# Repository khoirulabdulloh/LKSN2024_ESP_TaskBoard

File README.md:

# LKSN2024_ESP_TaskBoard
Embedded System Programming Task Board for Lomba Kompetensi Siswa Nasional Tahun 2024

 -Template_Program berisi template untuk pemrogramaan saat lomba, template akan terus update hingga H-3 perlombaan
 
 -file *.sch* merupakan schematic file EAGLE atau Fusion360

 -file *.brd* merupakan layout file EAGLE atau Fusion360

 -Schematic .pdf merupakan schematic file yang sudah di export dalam PDF

 -file .png merupakan foto dari TaskProject

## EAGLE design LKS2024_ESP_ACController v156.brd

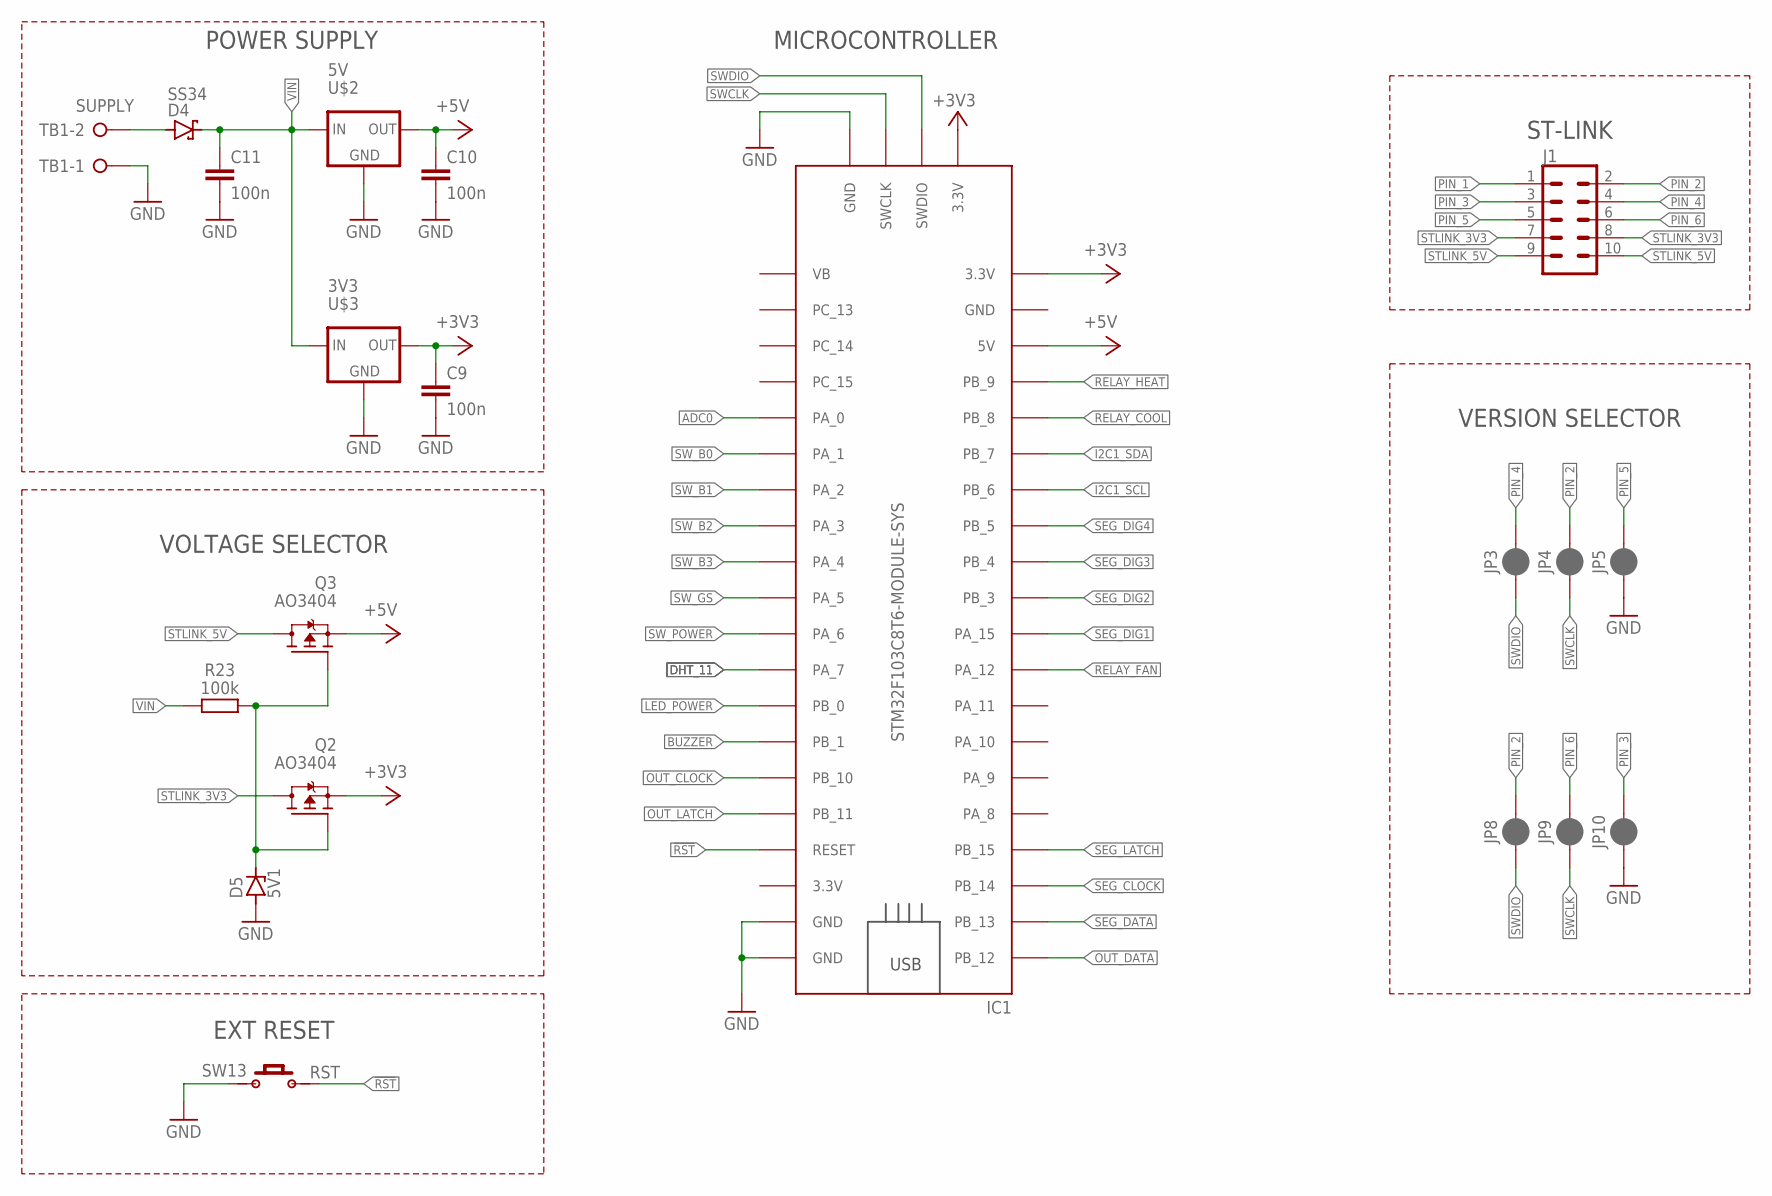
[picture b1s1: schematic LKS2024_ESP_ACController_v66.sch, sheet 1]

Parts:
C9, C10, C11: 100n; C0805
D4: SS34; SMA
D5: 5V1; SOD80C
IC1: STM32F103C8T6-MODULE-SYS
J1: CONN_05X2ML10L; ML10L
JP3, JP4, JP5, JP8, JP9, JP10: JUMPER-SMT_2_NC_PASTE_SILK; SMT-JUMPER_2_NC_PASTE_SILK
Q2, Q3: AO3404; SOT23
R23: 100k; R0805
SW13: RST; PUSH_BUTTON_2P
TB1: SUPPLY; MSTBA2
U$2: 5V; SOT223
U$3: 3V3; SOT223

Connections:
!RST: IC1.RESET, SW13.2
+3V3: C9.1, IC1.3.3V_1 (3.3V), IC1.3V3_1 (3.3V), IC1.3V3_3 (3.3V), Q2.2 (S), U$3.2 (OUT); also elsewhere on the board
+5V: C10.1, IC1.5V, Q3.2 (S), U$2.2 (OUT); also elsewhere on the board
ADC0: IC1.PA_0; also elsewhere on the board
BUZZER: IC1.PB_1; also elsewhere on the board
DHT_11: IC1.PA_7; also elsewhere on the board
GND: C9.2, C10.2, C11.2, D5.A, IC1.GND_2 (GND), IC1.GND_3 (GND), IC1.GND_4 (GND), IC1.GND_5 (GND), JP5.1, JP10.1, SW13.1, TB1.1, U$2.1 (GND), U$3.1 (GND); also elsewhere on the board
I2C1_SCL: IC1.PB_6; also elsewhere on the board
I2C1_SDA: IC1.PB_7; also elsewhere on the board
LED_POWER: IC1.PB_0; also elsewhere on the board
unnamed: D4.A, TB1.2
unnamed: D5.C, Q2.1 (G), Q3.1 (G), R23.2
OUT_CLOCK: IC1.PB_10; also elsewhere on the board
OUT_DATA: IC1.PB_12; also elsewhere on the board
OUT_LATCH: IC1.PB_11; also elsewhere on the board
PIN_1: J1.1
PIN_2: J1.2, JP4.2, JP8.2
PIN_3: J1.3, JP10.2
PIN_4: J1.4, JP3.2
PIN_5: J1.5, JP5.2
PIN_6: J1.6, JP9.2
RELAY_COOL: IC1.PB_8; also elsewhere on the board
RELAY_FAN: IC1.PA_12; also elsewhere on the board
RELAY_HEAT: IC1.PB_9; also elsewhere on the board
SEG_CLOCK: IC1.PB_14; also elsewhere on the board
SEG_DATA: IC1.PB_13; also elsewhere on the board
SEG_DIG1: IC1.PA_15; also elsewhere on the board
SEG_DIG2: IC1.PB_3; also elsewhere on the board
SEG_DIG3: IC1.PB_4; also elsewhere on the board
SEG_DIG4: IC1.PB_5; also elsewhere on the board
SEG_LATCH: IC1.PB_15; also elsewhere on the board
STLINK_3V3: J1.7, J1.8, Q2.3 (D)
STLINK_5V: J1.9, J1.10, Q3.3 (D)
SWCLK: IC1.SWCLK, IC1.SWCLK1 (SWCLK), JP4.1, JP9.1
SWDIO: IC1.SWDIO, IC1.SWDIO1 (SWDIO), JP3.1, JP8.1
SW_B0: IC1.PA_1; also elsewhere on the board
SW_B1: IC1.PA_2; also elsewhere on the board
SW_B2: IC1.PA_3; also elsewhere on the board
SW_B3: IC1.PA_4; also elsewhere on the board
SW_GS: IC1.PA_5; also elsewhere on the board
SW_POWER: IC1.PA_6; also elsewhere on the board
VIN: C11.1, D4.C, R23.1, U$2.3 (IN), U$3.3 (IN)

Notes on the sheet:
POWER SUPPLY
VOLTAGE SELECTOR
EXT RESET
ST-LINK
VERSION SELECTOR
MICROCONTROLLER

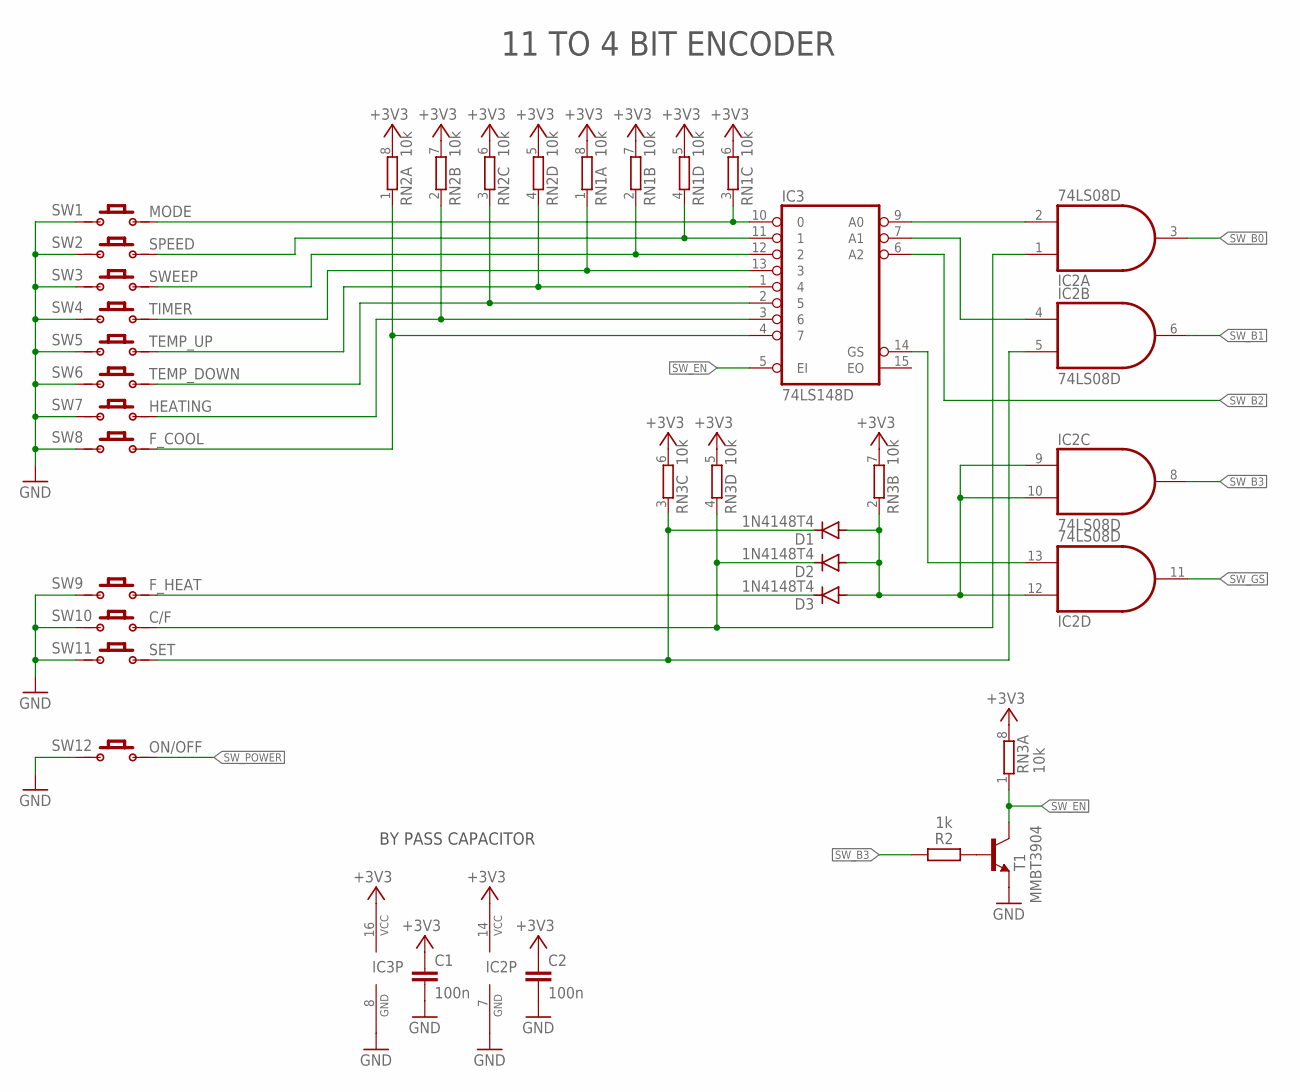
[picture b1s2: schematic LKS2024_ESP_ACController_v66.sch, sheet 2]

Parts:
C1, C2: 100n; C0805
D1, D2, D3: 1N4148T4; SOD123
IC2: 74LS08D; SO14
IC3: 74LS148D; SO16
R2: 1k; R0805
RN1, RN2, RN3: 10k; 0603-ARC
SW1: MODE; PUSH_BUTTON_2P
SW2: SPEED; PUSH_BUTTON_2P
SW3: SWEEP; PUSH_BUTTON_2P
SW4: TIMER; PUSH_BUTTON_2P
SW5: TEMP_UP; PUSH_BUTTON_2P
SW6: TEMP_DOWN; PUSH_BUTTON_2P
SW7: HEATING; PUSH_BUTTON_2P
SW8: F_COOL; PUSH_BUTTON_2P
SW9: F_HEAT; PUSH_BUTTON_2P
SW10: C/F; PUSH_BUTTON_2P
SW11: SET; PUSH_BUTTON_2P
SW12: ON/OFF; PUSH_BUTTON_2P
T1: MMBT3904; SOT23-BEC

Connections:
+3V3: C1.1, C2.1, IC2.14 (VCC), IC3.16 (VCC), RN1.5 (2), RN1.6 (2), RN1.7 (2), RN1.8 (2), RN2.5 (2), RN2.6 (2), RN2.7 (2), RN2.8 (2), RN3.5 (2), RN3.6 (2), RN3.7 (2), RN3.8 (2); also elsewhere on the board
GND: C1.2, C2.2, IC2.7 (GND), IC3.8 (GND), SW1.1, SW2.1, SW3.1, SW4.1, SW5.1, SW6.1, SW7.1, SW8.1, SW9.1, SW10.1, SW11.1, SW12.1, T1.E; also elsewhere on the board
unnamed: IC2.2 (I1), IC3.9 (A0)
unnamed: IC2.4 (I0), IC3.7 (A1)
unnamed: IC2.13 (I1), IC3.14 (GS)
unnamed: D1.A, D2.A, D3.A, IC2.9 (I0), IC2.10 (I1), IC2.12 (I0), RN3.2 (1)
unnamed: IC3.10 (0), RN1.3 (1), SW1.2
unnamed: IC3.11 (1), RN1.4 (1), SW2.2
unnamed: IC3.12 (2), RN1.2 (1), SW3.2
unnamed: IC3.13 (3), RN1.1, SW4.2
unnamed: IC3.1 (4), RN2.4 (1), SW5.2
unnamed: IC3.2 (5), RN2.3 (1), SW6.2
unnamed: IC3.3 (6), RN2.2 (1), SW7.2
unnamed: IC3.4 (7), RN2.1, SW8.2
unnamed: D3.C, SW9.2
unnamed: D2.C, IC2.1 (I0), RN3.4 (1), SW10.2
unnamed: D1.C, IC2.5 (I1), RN3.3 (1), SW11.2
unnamed: R2.1, T1.B
SW_B0: IC2.3 (O); also elsewhere on the board
SW_B1: IC2.6 (O); also elsewhere on the board
SW_B2: IC3.6 (A2); also elsewhere on the board
SW_B3: IC2.8 (O), R2.2; also elsewhere on the board
SW_EN: IC3.5 (EI), RN3.1, T1.C
SW_GS: IC2.11 (O); also elsewhere on the board
SW_POWER: SW12.2; also elsewhere on the board

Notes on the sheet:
11 TO 4 BIT ENCODER
BY PASS CAPACITOR

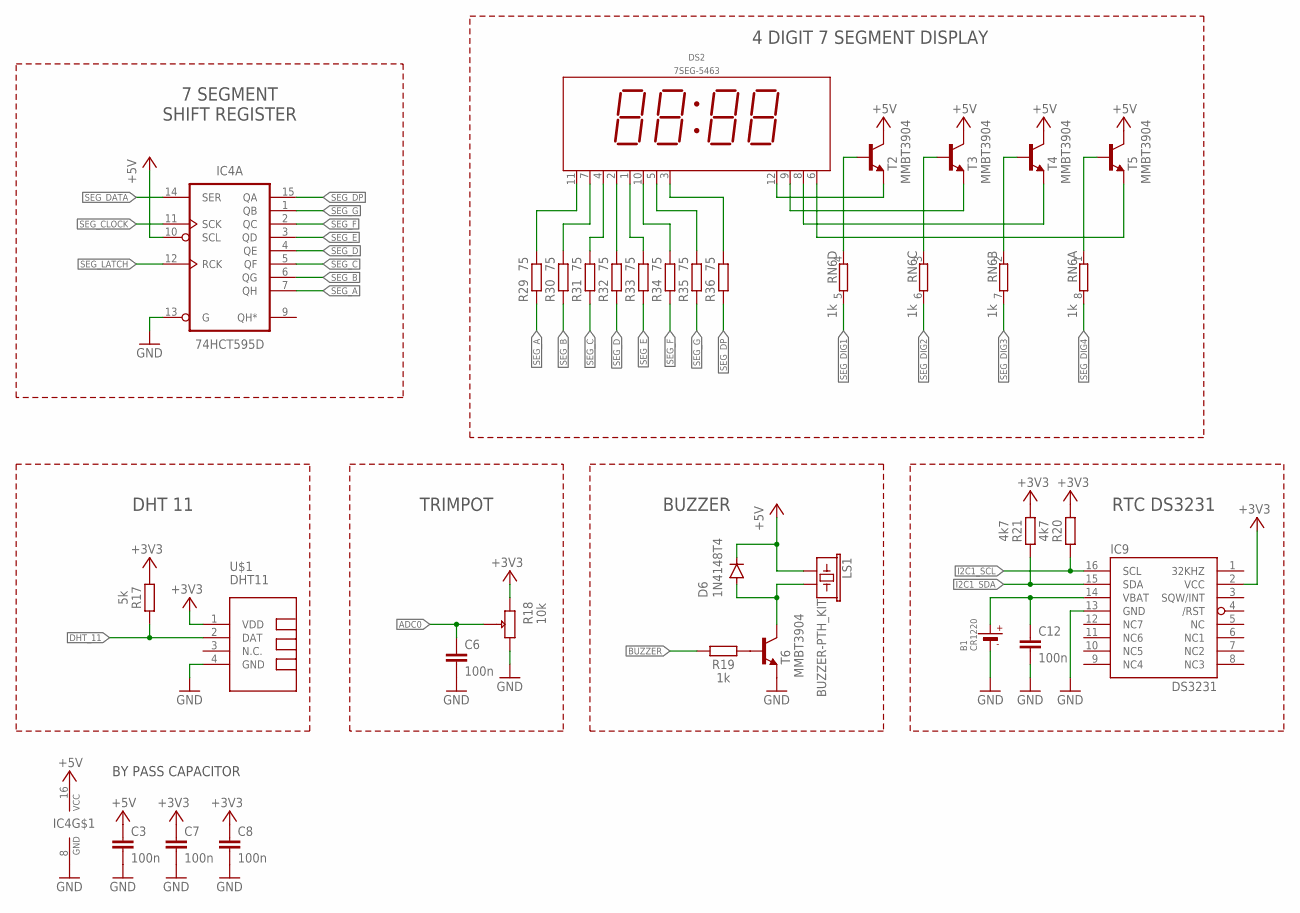
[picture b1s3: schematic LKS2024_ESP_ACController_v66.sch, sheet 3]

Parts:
B1: CR1220
C3, C6, C7, C8, C12: 100n; C0805
D6: 1N4148T4; SOD123
DS2: 7SEG-5463; 5643
IC4: 74HCT595D; SO16
IC9: DS3231"; SO16W
LS1: BUZZER-PTH_KIT; BUZZER-12MM-KIT
R17: 5k; R0805
R18: 10k; TRIM_3386P-1-101T
R19: 1k; R0805
R20, R21: 4k7; R0805
R29, R30, R31, R32, R33, R34, R35, R36: 75; R0603
RN6: 1k; 0603-ARC
T2, T3, T4, T5, T6: MMBT3904; SOT23-BEC
U$1: DHT11

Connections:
+3V3: C7.1, C8.1, IC9.2 (VCC), R17.1, R18.3 (CW), R20.2, R21.2, U$1.1 (VDD); also elsewhere on the board
+5V: C3.1, D6.C, IC4.10 (SCL), IC4.16 (VCC), LS1.+\ (1), T2.C, T3.C, T4.C, T5.C; also elsewhere on the board
ADC0: C6.1, R18.2 (WIPER); also elsewhere on the board
BUZZER: R19.1; also elsewhere on the board
DHT_11: R17.2, U$1.2 (DAT); also elsewhere on the board
GND: B1.-, C3.2, C6.2, C7.2, C8.2, C12.2, IC4.8 (GND), IC4.13 (G), IC9.13 (GND), R18.1 (CCW), T6.E, U$1.4 (GND); also elsewhere on the board
I2C1_SCL: IC9.16 (SCL), R20.1; also elsewhere on the board
I2C1_SDA: IC9.15 (SDA), R21.1; also elsewhere on the board
unnamed: DS2.12 (DIG1), T2.E
unnamed: DS2.11 (A), R29.2
unnamed: DS2.7 (B), R30.2
unnamed: DS2.4 (C), R31.2
unnamed: DS2.2 (D), R32.2
unnamed: DS2.1 (E), R33.2
unnamed: DS2.10 (F), R34.2
unnamed: DS2.5 (G), R35.2
unnamed: DS2.3 (H), R36.2
unnamed: RN6.4 (1), T2.B
unnamed: DS2.9 (DIG2), T3.E
unnamed: DS2.8 (DIG3), T4.E
unnamed: DS2.6 (DIG4), T5.E
unnamed: RN6.3 (1), T3.B
unnamed: RN6.2 (1), T4.B
unnamed: RN6.1, T5.B
unnamed: D6.A, LS1.- (2), T6.C
unnamed: R19.2, T6.B
unnamed: B1.+, C12.1, IC9.14 (VBAT)
SEG_A: IC4.7 (QH), R29.1
SEG_B: IC4.6 (QG), R30.1
SEG_C: IC4.5 (QF), R31.1
SEG_CLOCK: IC4.11 (SCK); also elsewhere on the board
SEG_D: IC4.4 (QE), R32.1
SEG_DATA: IC4.14 (SER); also elsewhere on the board
SEG_DIG1: RN6.5 (2); also elsewhere on the board
SEG_DIG2: RN6.6 (2); also elsewhere on the board
SEG_DIG3: RN6.7 (2); also elsewhere on the board
SEG_DIG4: RN6.8 (2); also elsewhere on the board
SEG_DP: IC4.15 (QA), R36.1
SEG_E: IC4.3 (QD), R33.1
SEG_F: IC4.2 (QC), R34.1
SEG_G: IC4.1 (QB), R35.1
SEG_LATCH: IC4.12 (RCK); also elsewhere on the board

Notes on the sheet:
4 DIGIT 7 SEGMENT DISPLAY
7 SEGMENT SHIFT REGISTER
RTC DS3231
BUZZER
TRIMPOT
DHT 11
BY PASS CAPACITOR

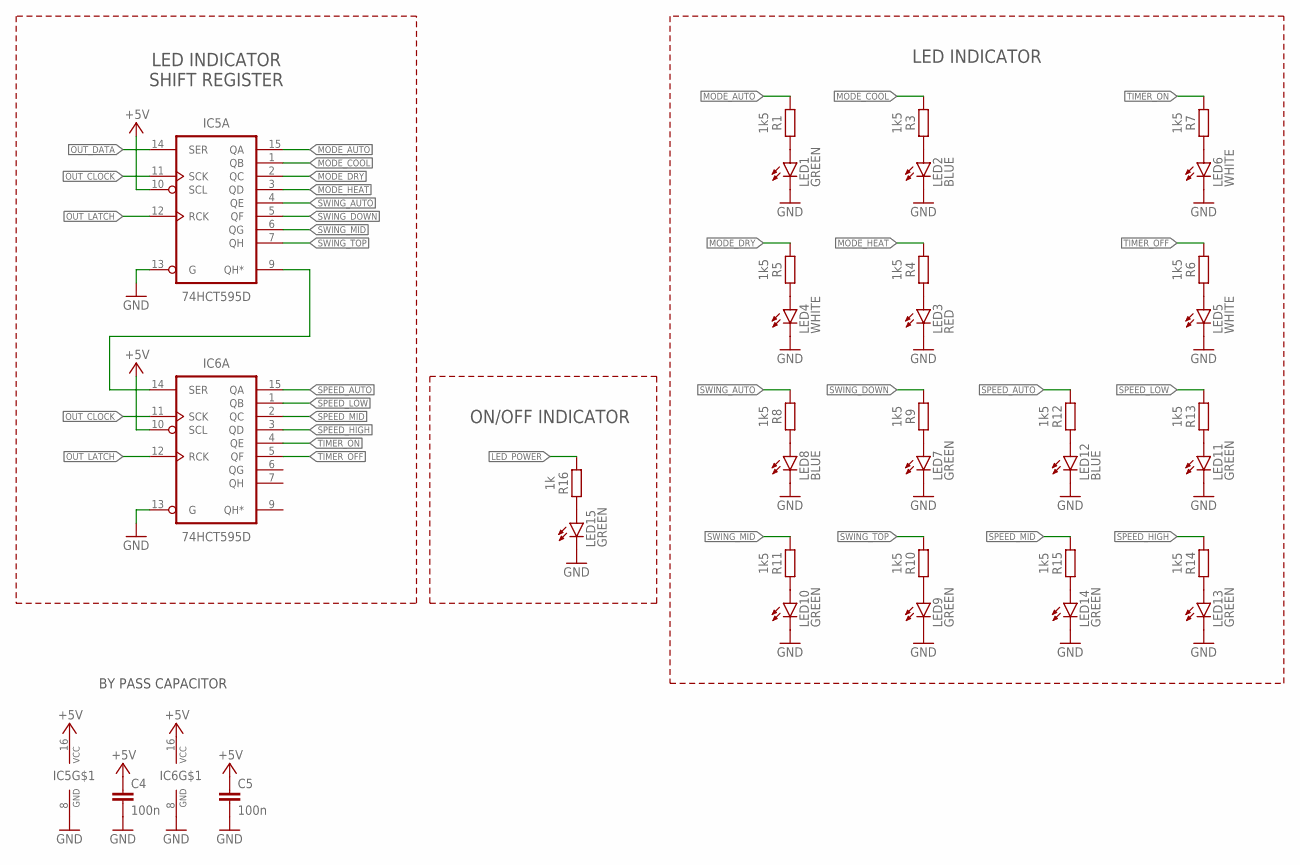
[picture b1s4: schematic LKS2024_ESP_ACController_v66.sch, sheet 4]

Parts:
C4, C5: 100n; C0805
IC5, IC6: 74HCT595D; SO16
LED1, LED7, LED9, LED10, LED11, LED13, LED14, LED15: GREEN; CHIPLED_1206
LED2, LED8, LED12: BLUE; CHIPLED_1206
LED3: RED; CHIPLED_1206
LED4, LED5, LED6: WHITE; CHIPLED_1206
R1, R3, R4, R5, R6, R7, R8, R9, R10, R11, R12, R13, R14, R15: 1k5; R0805
R16: 1k; R0805

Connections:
+5V: C4.1, C5.1, IC5.10 (SCL), IC5.16 (VCC), IC6.10 (SCL), IC6.16 (VCC); also elsewhere on the board
GND: C4.2, C5.2, IC5.8 (GND), IC5.13 (G), IC6.8 (GND), IC6.13 (G), LED1.C, LED2.C, LED3.C, LED4.C, LED5.C, LED6.C, LED7.C, LED8.C, LED9.C, LED10.C, LED11.C, LED12.C, LED13.C, LED14.C, LED15.C; also elsewhere on the board
LED_POWER: R16.1; also elsewhere on the board
MODE_AUTO: IC5.15 (QA), R1.1
MODE_COOL: IC5.1 (QB), R3.1
MODE_DRY: IC5.2 (QC), R5.1
MODE_HEAT: IC5.3 (QD), R4.1
unnamed: IC5.9 (QH*), IC6.14 (SER)
unnamed: LED1.A, R1.2
unnamed: LED2.A, R3.2
unnamed: LED3.A, R4.2
unnamed: LED4.A, R5.2
unnamed: LED5.A, R6.2
unnamed: LED6.A, R7.2
unnamed: LED8.A, R8.2
unnamed: LED7.A, R9.2
unnamed: LED9.A, R10.2
unnamed: LED10.A, R11.2
unnamed: LED12.A, R12.2
unnamed: LED11.A, R13.2
unnamed: LED13.A, R14.2
unnamed: LED14.A, R15.2
unnamed: LED15.A, R16.2
OUT_CLOCK: IC5.11 (SCK), IC6.11 (SCK); also elsewhere on the board
OUT_DATA: IC5.14 (SER); also elsewhere on the board
OUT_LATCH: IC5.12 (RCK), IC6.12 (RCK); also elsewhere on the board
SPEED_AUTO: IC6.15 (QA), R12.1
SPEED_HIGH: IC6.3 (QD), R14.1
SPEED_LOW: IC6.1 (QB), R13.1
SPEED_MID: IC6.2 (QC), R15.1
SWING_AUTO: IC5.4 (QE), R8.1
SWING_DOWN: IC5.5 (QF), R9.1
SWING_MID: IC5.6 (QG), R11.1
SWING_TOP: IC5.7 (QH), R10.1
TIMER_OFF: IC6.5 (QF), R6.1
TIMER_ON: IC6.4 (QE), R7.1

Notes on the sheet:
LED INDICATOR
ON/OFF INDICATOR
LED INDICATOR SHIFT REGISTER
BY PASS CAPACITOR

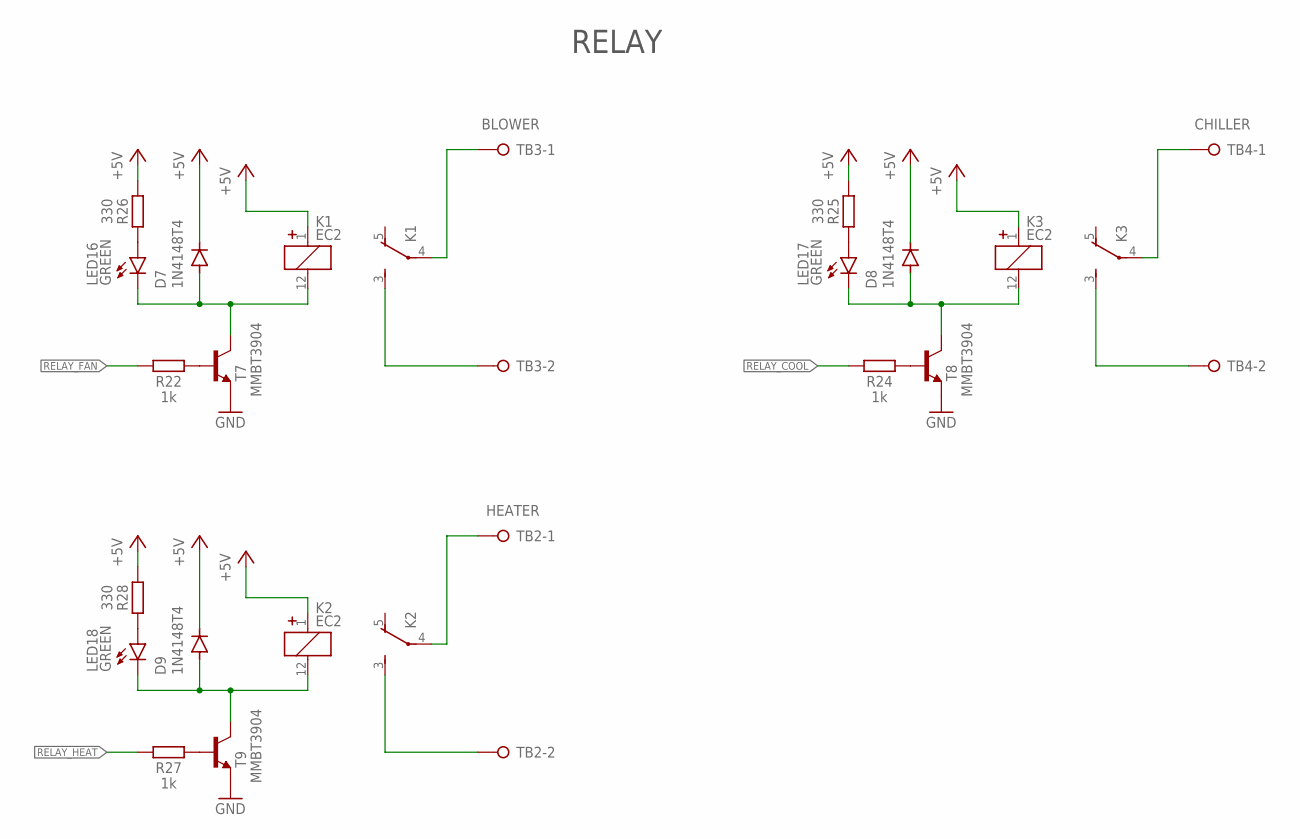
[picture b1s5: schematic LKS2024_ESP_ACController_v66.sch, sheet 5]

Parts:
D7, D8, D9: 1N4148T4; SOD123
K1, K2, K3: EC2
LED16, LED17, LED18: GREEN; CHIPLED_1206
R22, R24, R27: 1k; R0805
R25, R26, R28: 330; R0805
T7, T8, T9: MMBT3904; SOT23-BEC
TB2: HEATER; MSTBA2
TB3: BLOWER; MSTBA2
TB4: CHILLER; MSTBA2

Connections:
+5V: D7.C, D8.C, D9.C, K1.1 (1+), K2.1 (1+), K3.1 (1+), R25.1, R26.1, R28.1; also elsewhere on the board
GND: T7.E, T8.E, T9.E; also elsewhere on the board
unnamed: D7.A, K1.12 (2-), LED16.C, T7.C
unnamed: R22.2, T7.B
unnamed: D8.A, K3.12 (2-), LED17.C, T8.C
unnamed: R24.2, T8.B
unnamed: LED17.A, R25.2
unnamed: K3.3 (S), TB4.2
unnamed: LED16.A, R26.2
unnamed: K1.3 (S), TB3.2
unnamed: K1.4, TB3.1
unnamed: K3.4, TB4.1
unnamed: D9.A, K2.12 (2-), LED18.C, T9.C
unnamed: R27.2, T9.B
unnamed: LED18.A, R28.2
unnamed: K2.3 (S), TB2.2
unnamed: K2.4, TB2.1
RELAY_COOL: R24.1; also elsewhere on the board
RELAY_FAN: R22.1; also elsewhere on the board
RELAY_HEAT: R27.1; also elsewhere on the board

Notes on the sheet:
RELAY

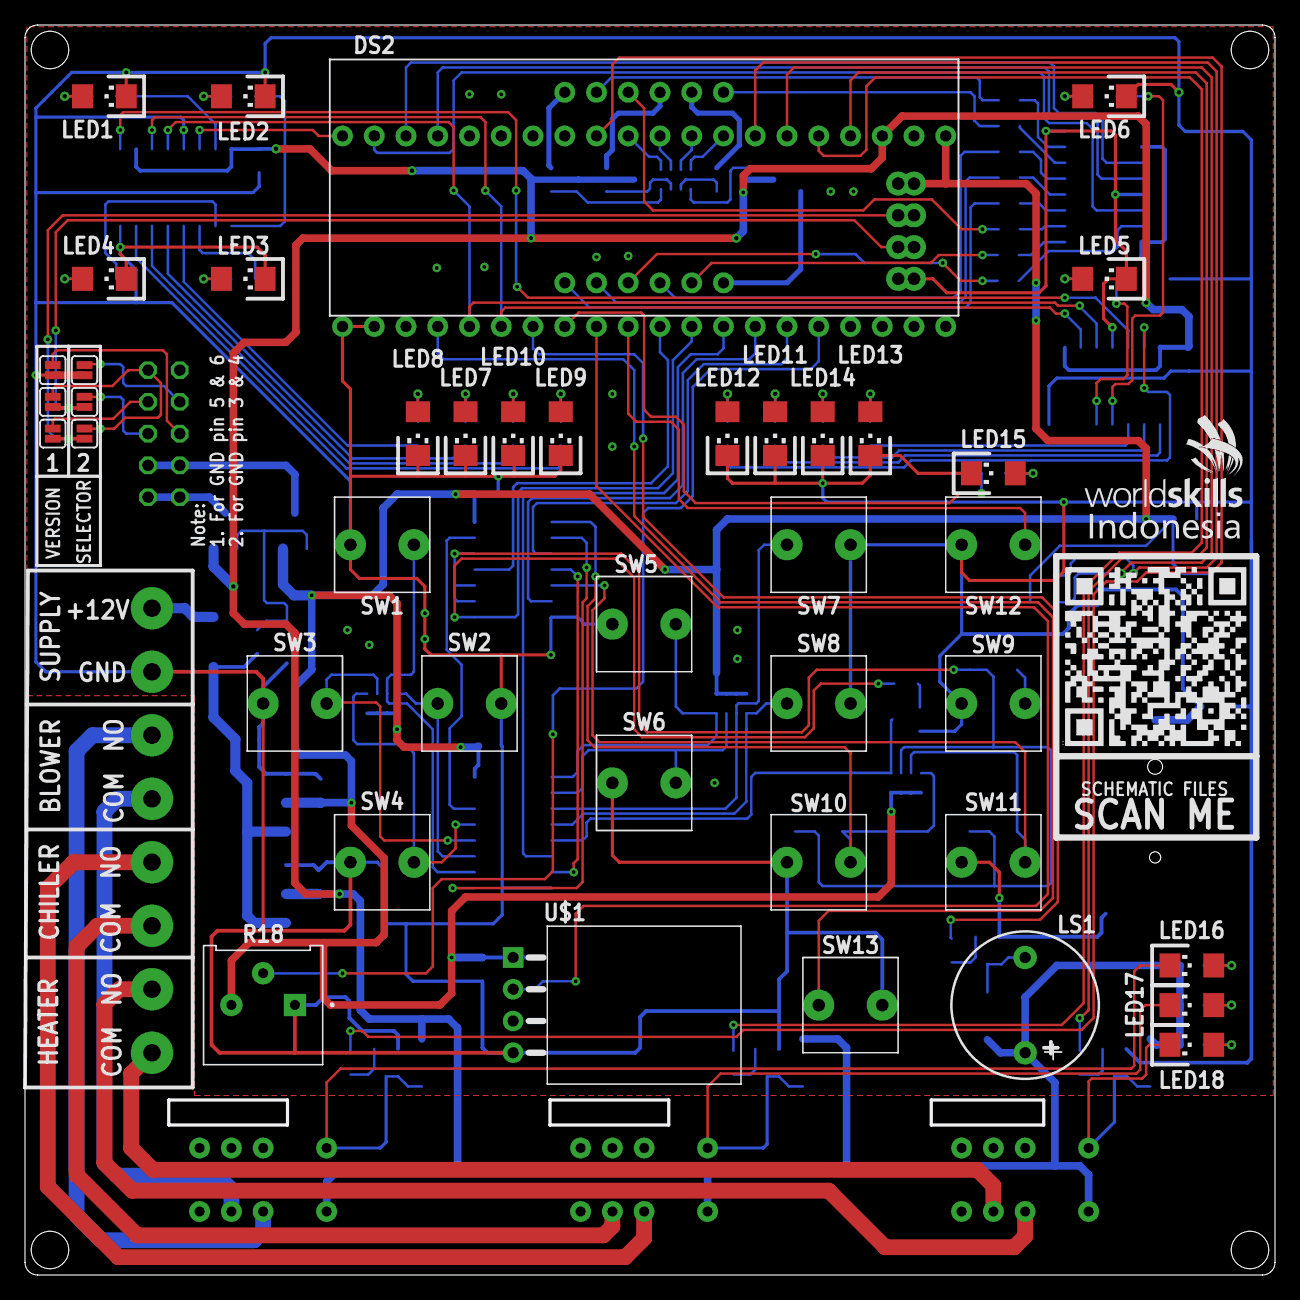
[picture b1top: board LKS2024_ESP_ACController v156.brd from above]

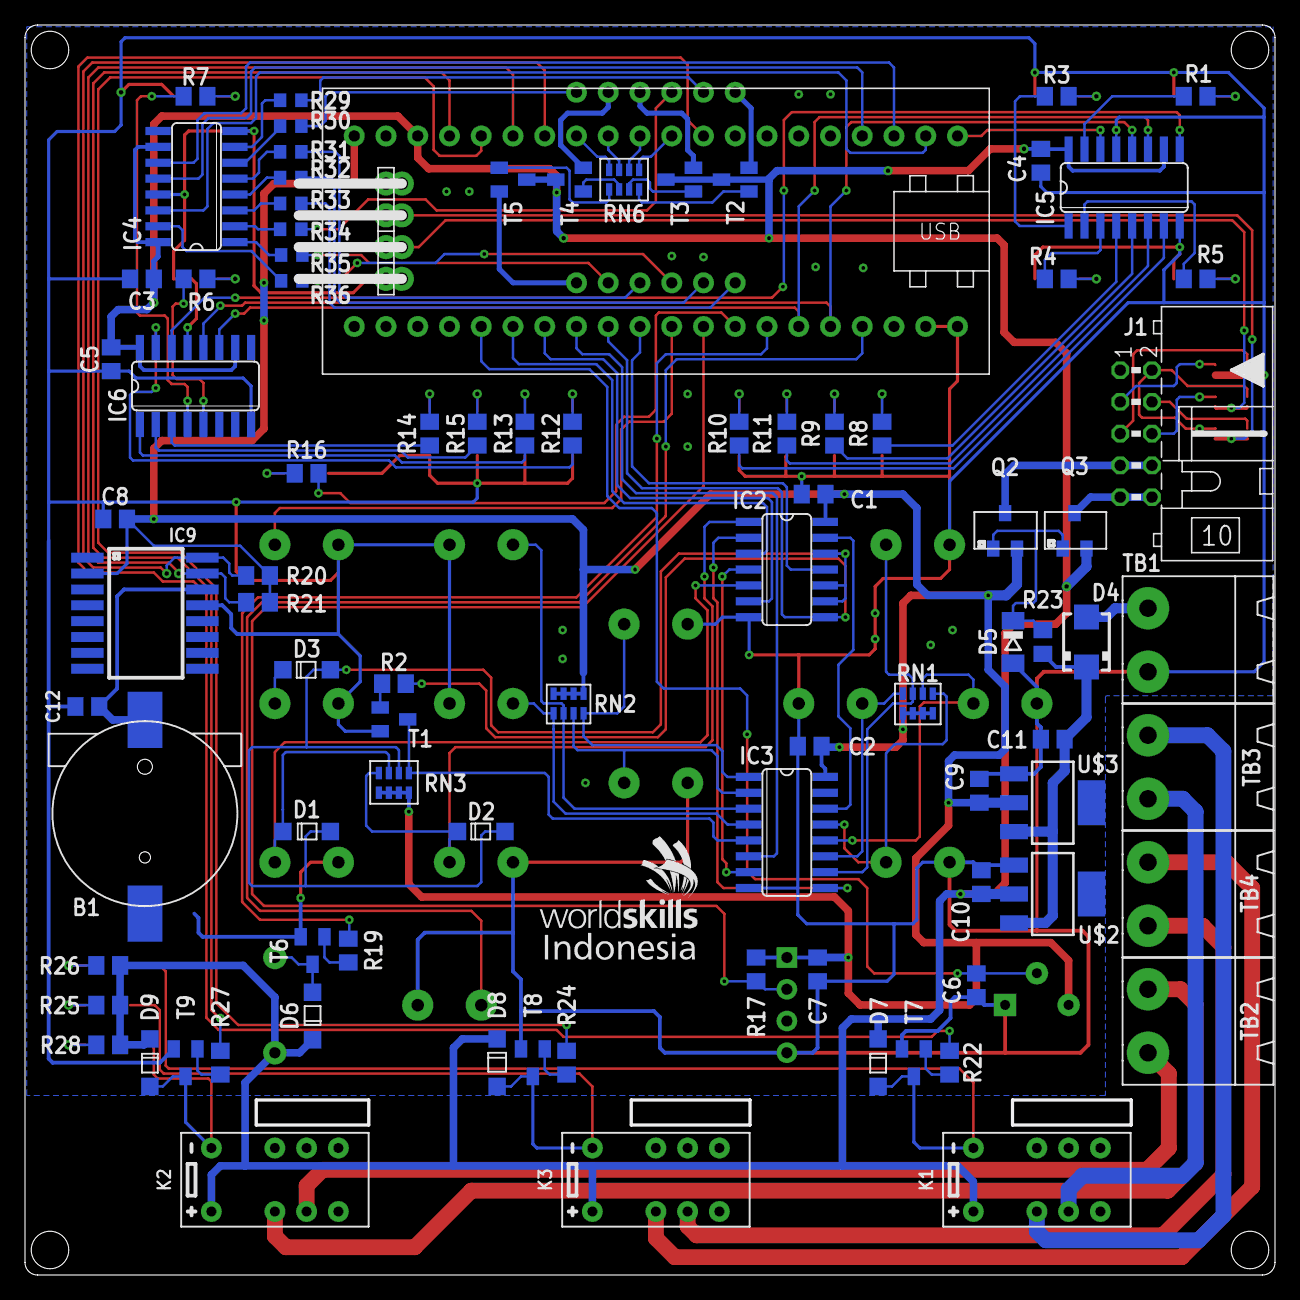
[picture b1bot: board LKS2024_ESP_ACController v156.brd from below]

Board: 2 copper layers, 99.7 x 99.7 mm, 130 parts (89 on the bottom side), 130 nets.

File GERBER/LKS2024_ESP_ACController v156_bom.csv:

Comment,Designator,Footprint,LCSC Part #
,J1,ML10L,
1N4148T4,D1 D2 D3 D6 D7 D8 D9,SOD123,
1k,RN6,0603-ARC,
1k,R2 R16 R19 R22 R24 R27,R0805,
1k5,R1 R3 R4 R5 R6 R7 R8 R9 R10 R11 R12 R13 R14 R15,R0805,
3V3,U$3,SOT223,
4k7,R20 R21,R0805,
5V,U$2,SOT223,
5V1,D5,SOD80C,
5k,R17,R0805,
7SEG-5463,DS2,5643,
10k,RN1 RN2 RN3,0603-ARC,
10k,R18,TRIM_3386P-1-101T,
74HCT595D,IC4 IC5 IC6,SO16,
74LS08D,IC2,SO14,
74LS148D,IC3,SO16,
75,R29 R30 R31 R32 R33 R34 R35 R36,R0603,
100k,R23,R0805,
100n,C1 C2 C3 C4 C5 C6 C7 C8 C9 C10 C11 C12,C0805,
330,R25 R26 R28,R0805,
AO3404,Q2 Q3,SOT23,
BLOWER,TB3,MSTBA2,
BLUE,LED2 LED8 LED12,CHIPLED_1206,
BUZZER-PTH_KIT,LS1,BUZZER-12MM-KIT,
C/F,SW10,PUSH_BUTTON_2P,
CHILLER,TB4,MSTBA2,
CR1220,B1,CR1220,
DHT11,U$1,DHT11,
DS3231",IC9,SO16W,
EC2,K1 K2 K3,EC2,
F_COOL,SW8,PUSH_BUTTON_2P,
F_HEAT,SW9,PUSH_BUTTON_2P,
GREEN,LED1 LED7 LED9 LED10 LED11 LED13 LED14 LED15 LED16 LED17 LED18,CHIPLED_1206,
HEATER,TB2,MSTBA2,
HEATING,SW7,PUSH_BUTTON_2P,
JUMPER-SMT_2_NC_PASTE_SILK,JP3 JP4 JP5 JP8 JP9 JP10,SMT-JUMPER_2_NC_PASTE_SILK,
MMBT3904,T1 T2 T3 T4 T5 T6 T7 T8 T9,SOT23-BEC,
MODE,SW1,PUSH_BUTTON_2P,
ON/OFF,SW12,PUSH_BUTTON_2P,
RED,LED3,CHIPLED_1206,
RST,SW13,PUSH_BUTTON_2P,
SET,SW11,PUSH_BUTTON_2P,
SPEED,SW2,PUSH_BUTTON_2P,
SS34,D4,SMA,
STM32F103C8T6-MODULE-SYS,IC1,STM32F103C8T6-MODULE-SYS,
SUPPLY,TB1,MSTBA2,
SWEEP,SW3,PUSH_BUTTON_2P,
TEMP_DOWN,SW6,PUSH_BUTTON_2P,
TEMP_UP,SW5,PUSH_BUTTON_2P,
TIMER,SW4,PUSH_BUTTON_2P,
WHITE,LED4 LED5 LED6,CHIPLED_1206,

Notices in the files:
parts and their libraries:
SparkFun-Jumpers: Licensing: Creative Commons ShareAlike 4.0 International - https://creativecommons.org/licenses/by-sa/4.0
